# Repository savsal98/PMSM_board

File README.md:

# PMSM_board
## В данном репозитории находится проект платы управления для СДПМ.

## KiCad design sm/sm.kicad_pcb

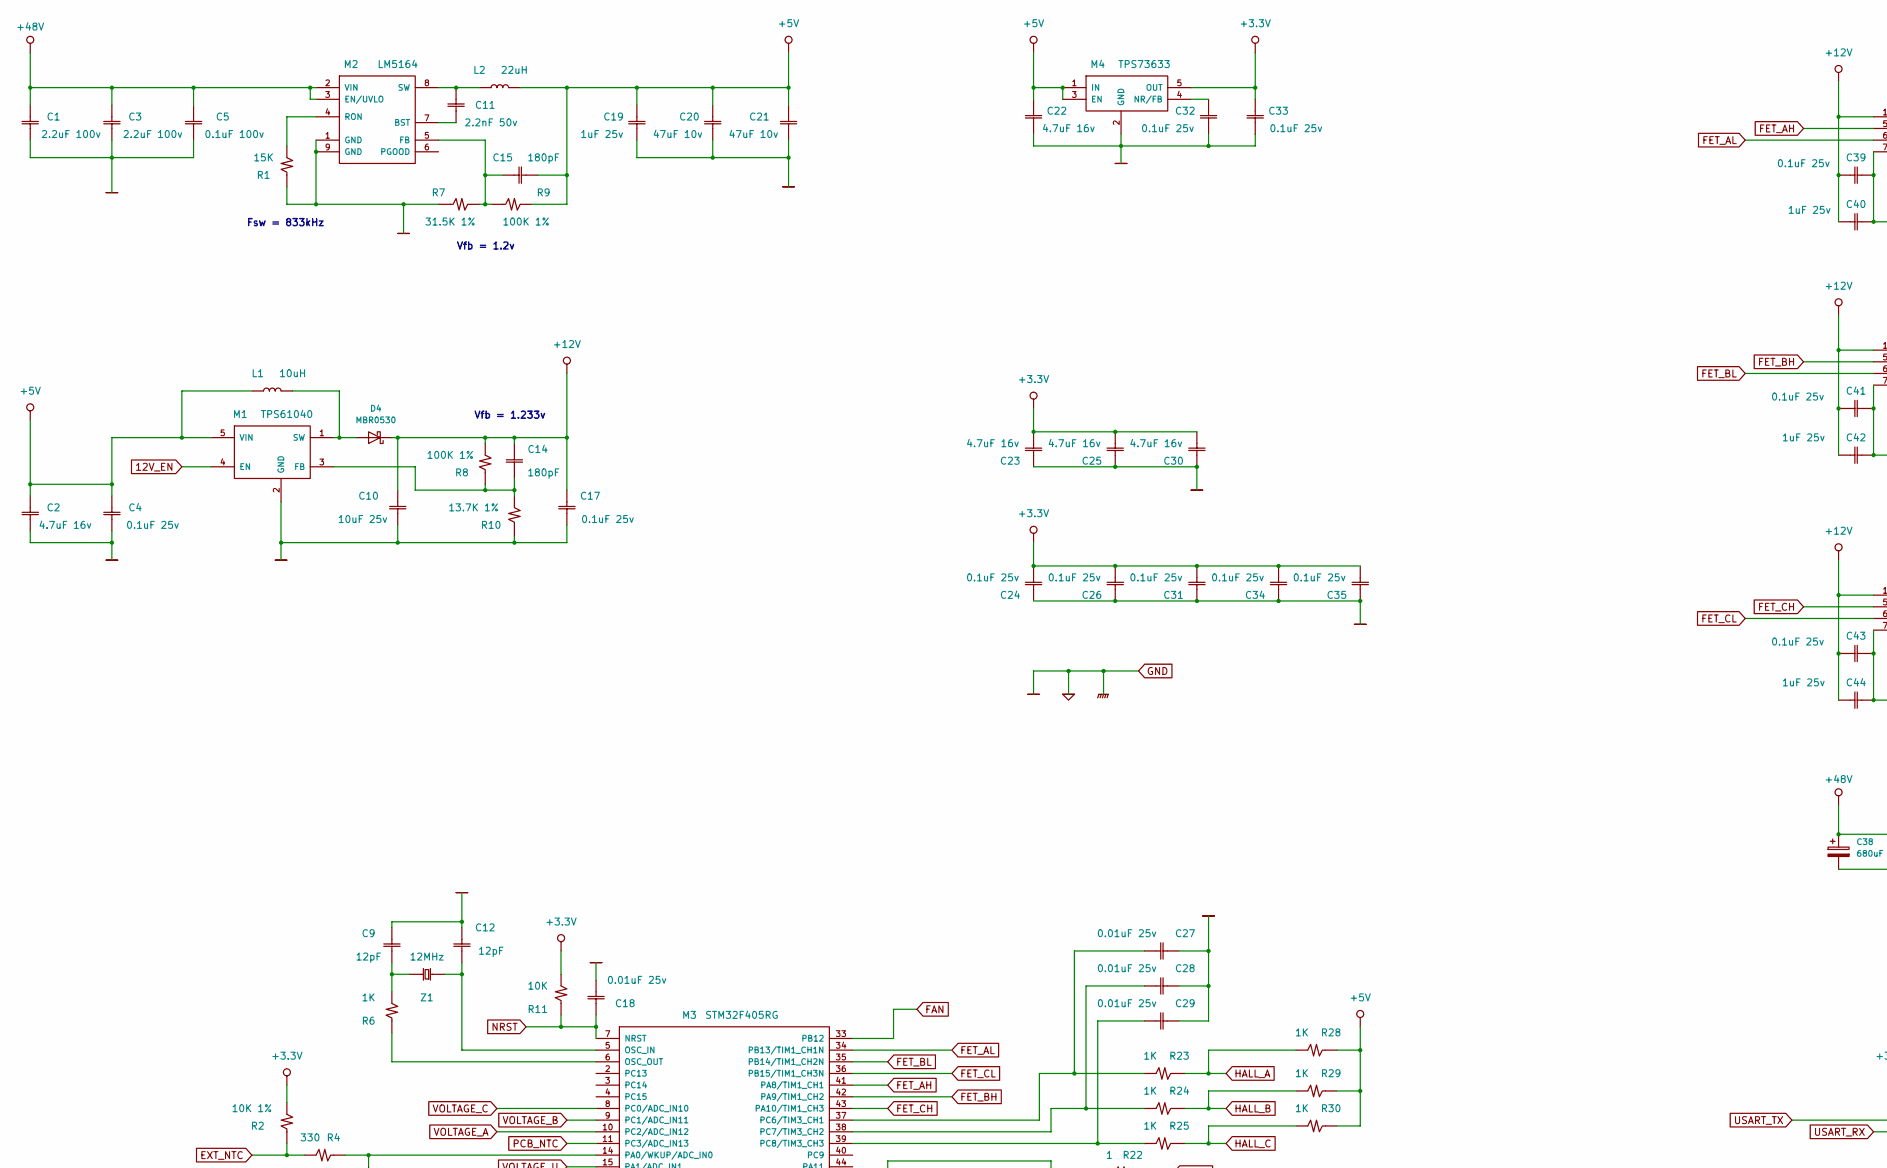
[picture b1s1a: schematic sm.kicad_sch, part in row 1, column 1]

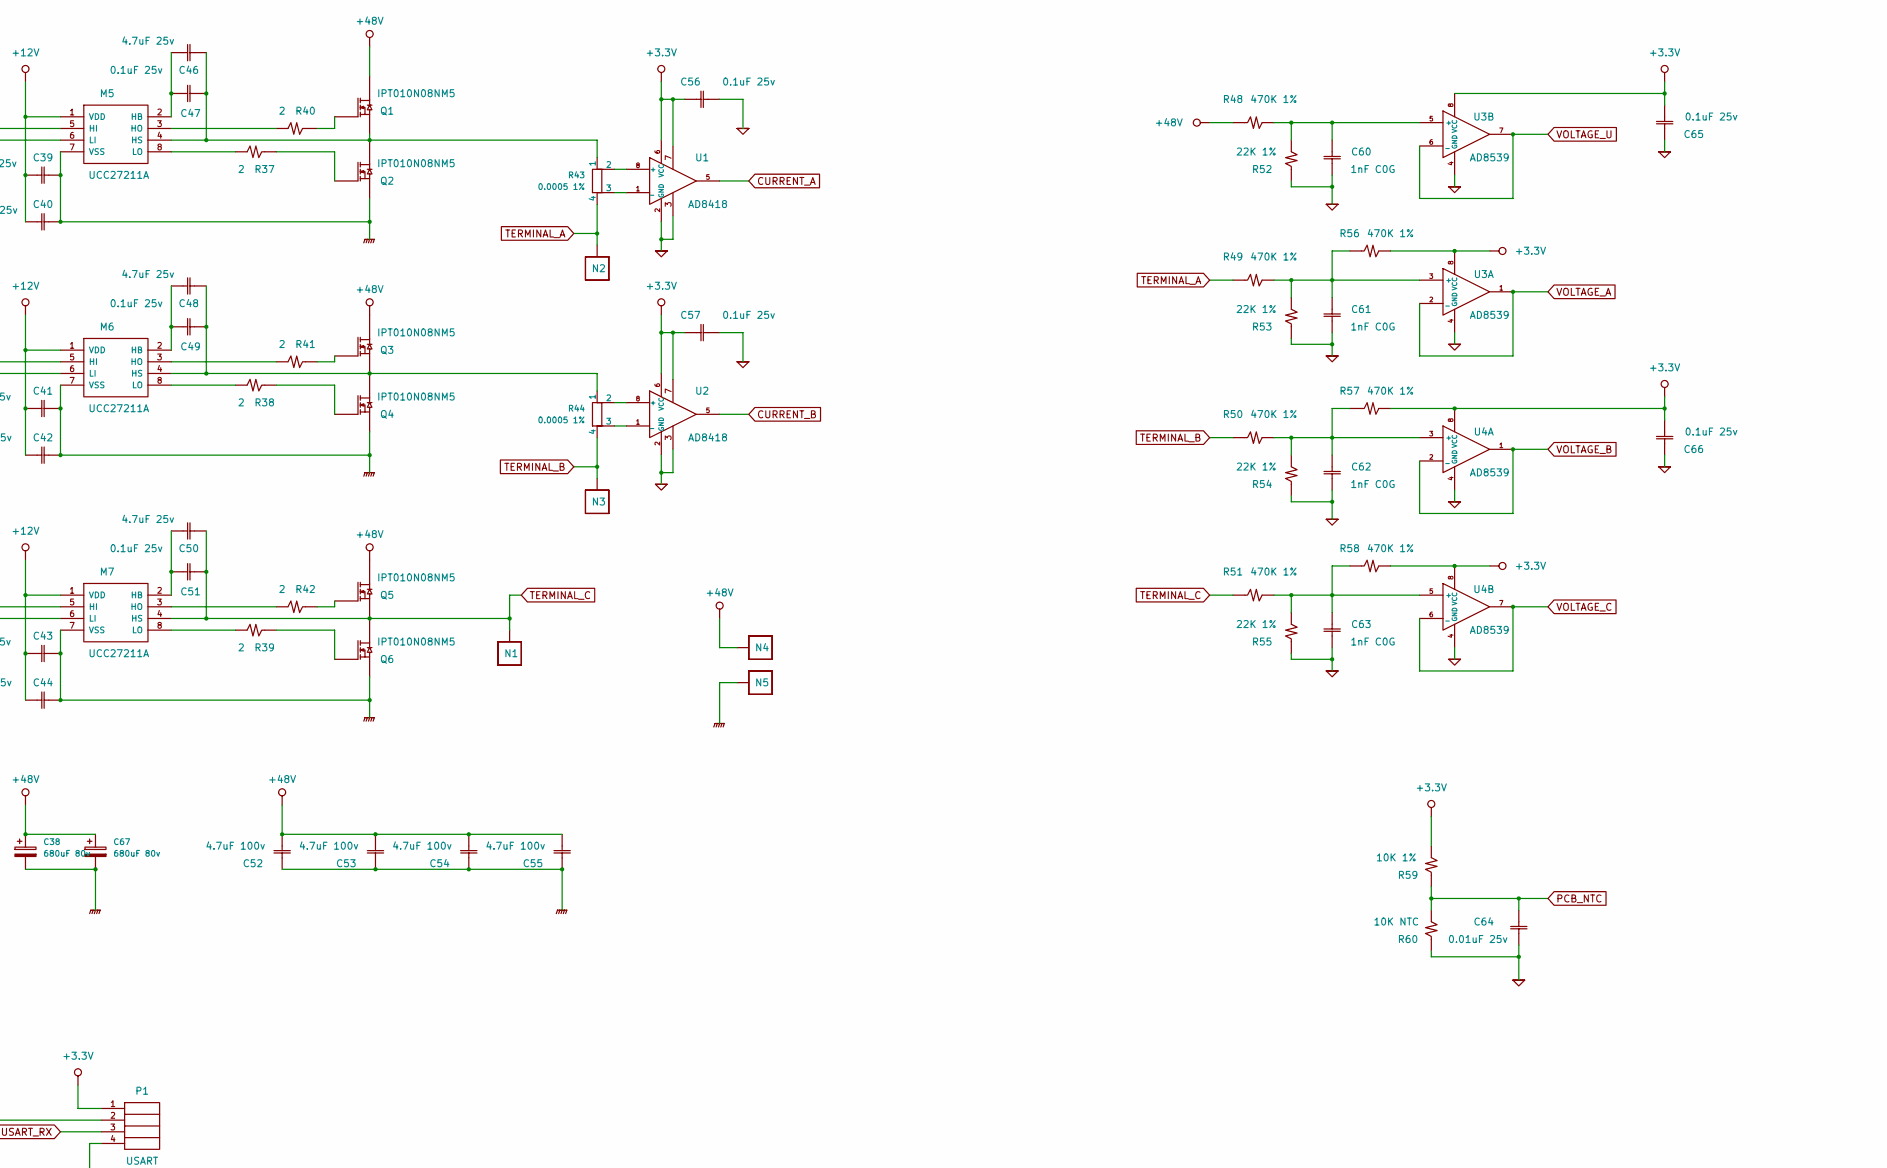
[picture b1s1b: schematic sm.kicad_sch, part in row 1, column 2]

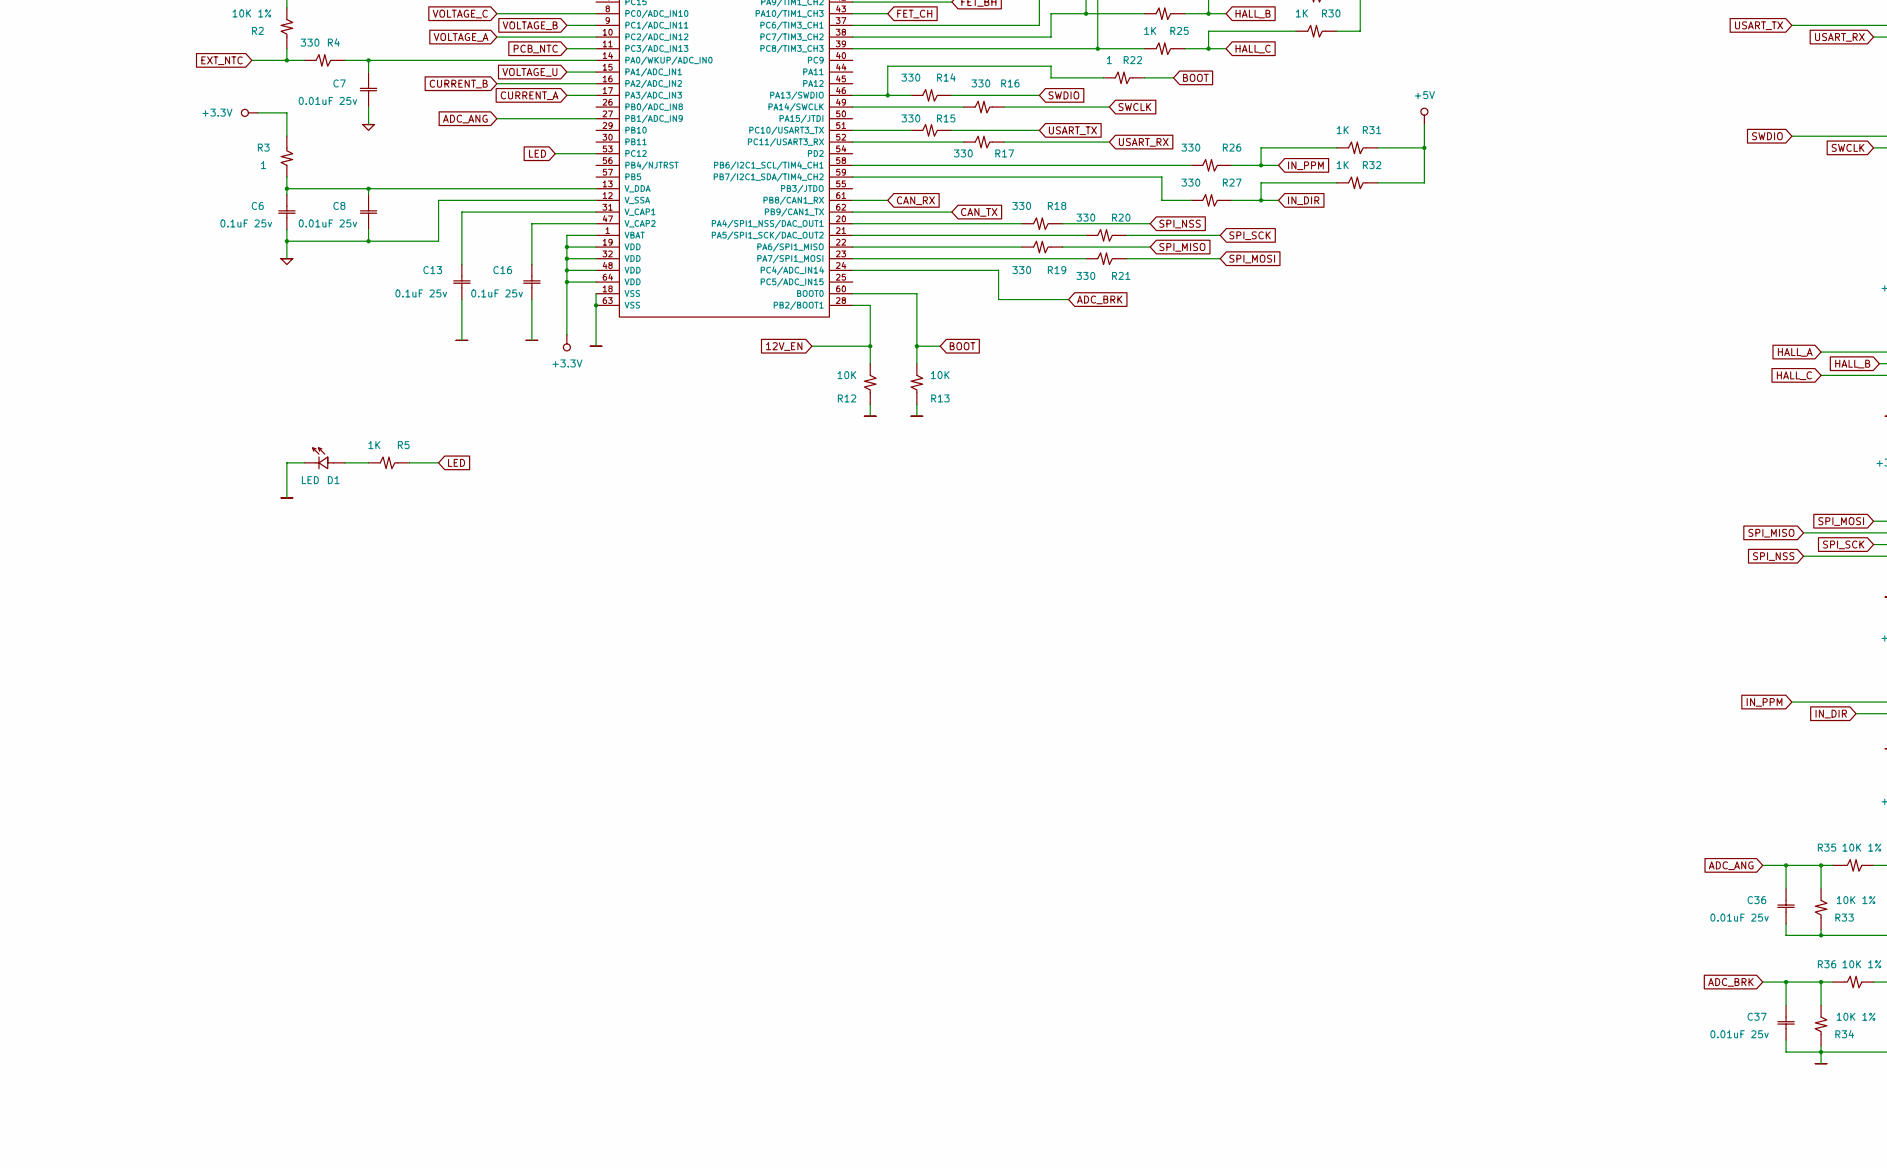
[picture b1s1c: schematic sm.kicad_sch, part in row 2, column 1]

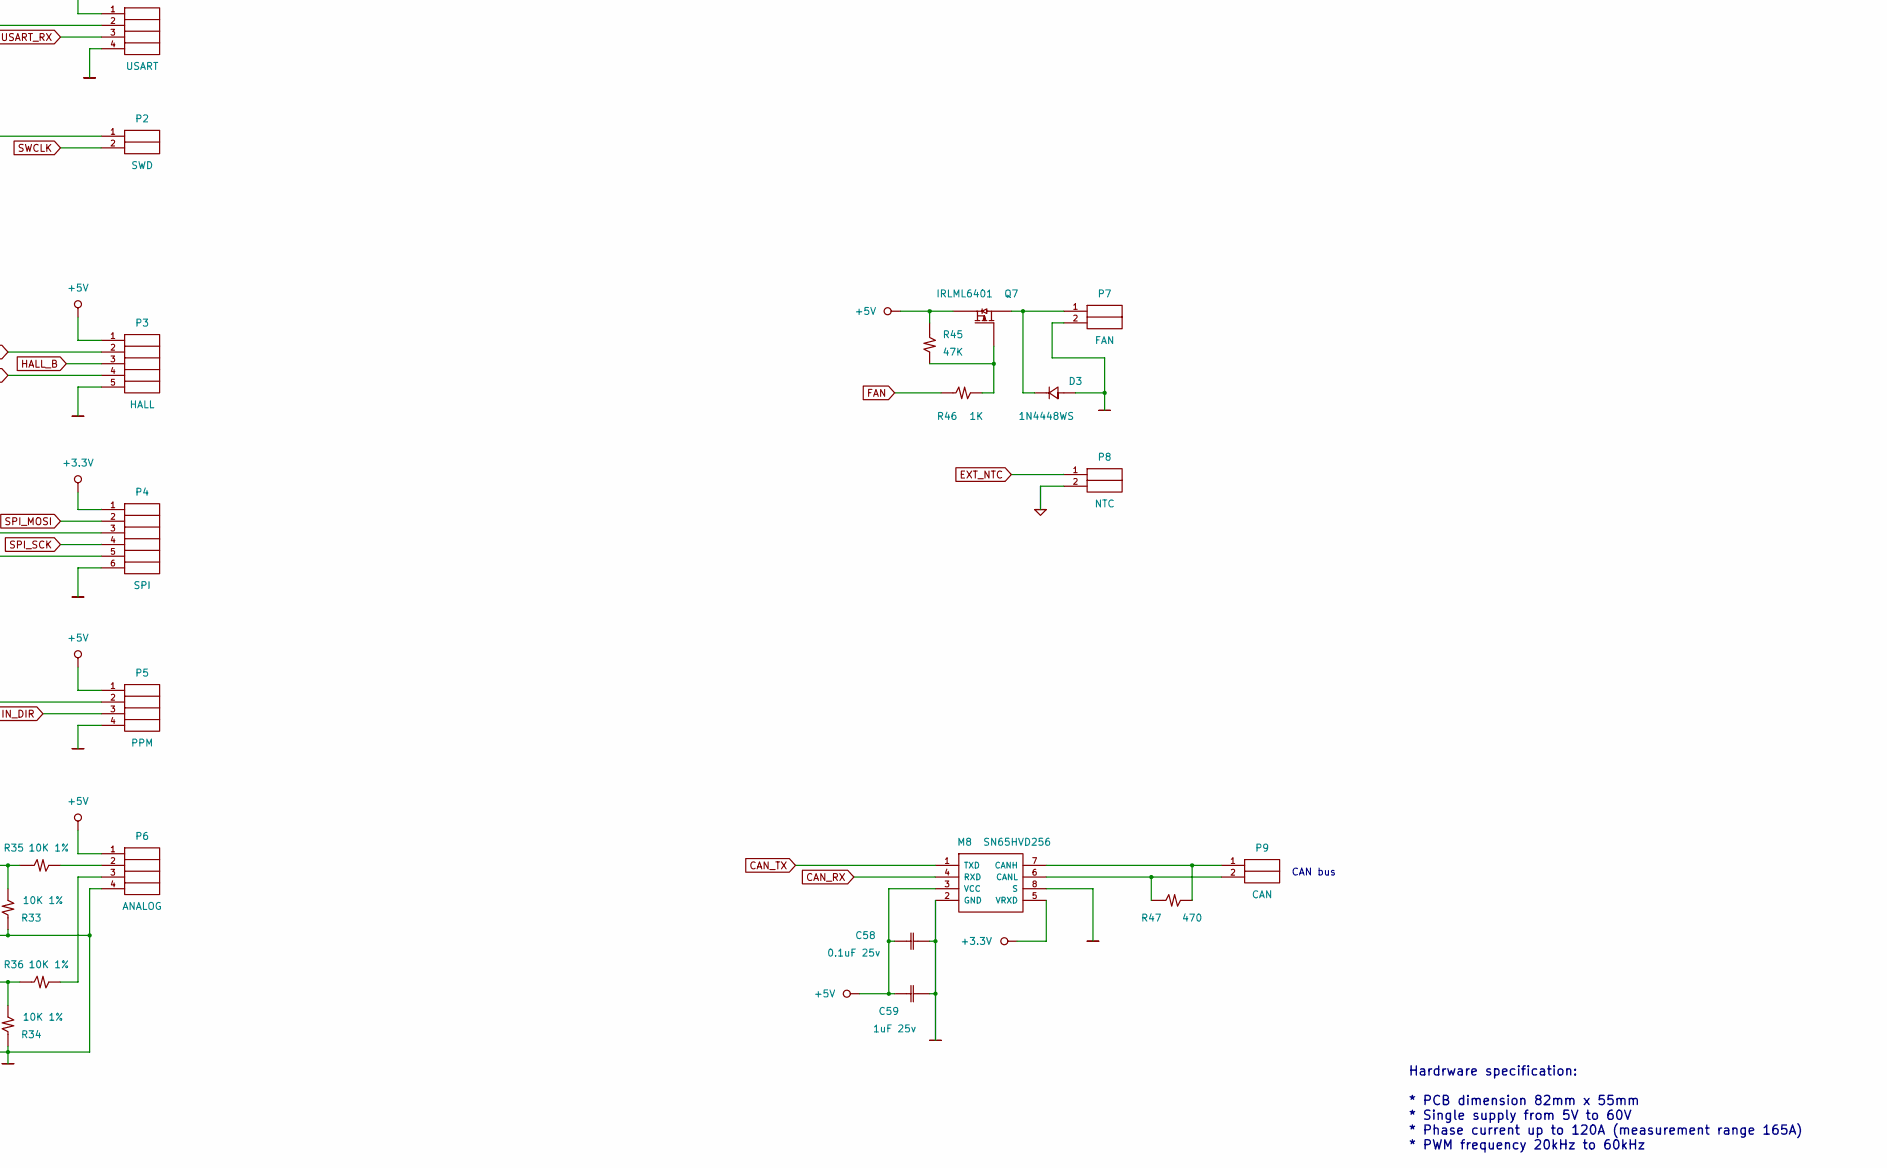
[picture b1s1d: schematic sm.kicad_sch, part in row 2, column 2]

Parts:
C1, C3: 2.2uF 100v; C_1210_3225Metric; LCSC C153036
C2, C22, C23, C25, C30: 4.7uF 16v; C_0805_2012Metric; LCSC C92762
C4, C6, C13, C16, C17, C24, C26, C31, C32, C33, C34, C35, C39, C41, C43, C47, C49, C51, C56, C57, C58, C65, C66: 0.1uF 25v; C_0805_2012Metric; LCSC C519981
C5: 0.1uF 100v; C_0805_2012Metric; LCSC C28233
C7, C8, C18, C27, C28, C29, C36, C37, C64: 0.01uF 25v; C_0603_1608Metric; LCSC C285099
C9, C12: 12pF; C_0603_1608Metric; LCSC C107034
C10: 10uF 25v; C_1210_3225Metric; LCSC C92834
C11: 2.2nF 50v; C_0805_2012Metric; LCSC C36576
C14, C15: 180pF; C_0603_1608Metric; LCSC C107041
C19, C40, C42, C44, C59: 1uF 25v; C_0805_2012Metric; LCSC C713511
C20, C21: 47uF 10v; C_1210_3225Metric; LCSC C5189825
C38, C67: 680uF 80v; CP_Radial_D16.0mm_P7.50mm; LCSC C443096
C46, C48, C50: 4.7uF 25v; C_0805_2012Metric; LCSC C1779
C52, C53, C54, C55: 4.7uF 100v; C_1210_3225Metric; LCSC C6120033
C60, C61, C62, C63: 1nF C0G; C_0603_1608Metric; LCSC C163508
D1: LED; LED_0603_1608Metric; LCSC C19171392
D3: 1N4448WS; D_0805_2012Metric; LCSC C109001
D4: MBR0530; D_SOD-123; LCSC C77336
L1: 10uH; L_Bourns_SRP1050WA; LCSC C7529415
L2: 22uH; L_Abracon_ASPI-0630LR; LCSC C7461363
M1: TPS61040; SOT-23-5; LCSC C7722
M2: LM5164; TI_SO-PowerPAD-8_ThermalVias; LCSC C477928
M3: STM32F405RG; LQFP-64_10x10mm_P0.5mm; LCSC C15742
M4: TPS73633; SOT-23-5; LCSC C28038
M5, M6, M7: UCC27211A; Texas_HSOP-8-1EP_3.9x4.9mm_P1.27mm_ThermalVias; LCSC C485921
M8: SN65HVD256; SOIC-8_3.9x4.9mm_P1.27mm; LCSC C132551
N1, N2, N3, N4, N5: PAD4; MountingHole_2.2mm_M2_Pad_Via
P1: USART; JST_PH_B4B-PH-K_1x04_P2.00mm_Vertical; LCSC C265289
P2: SWD; JST_PH_B2B-PH-K_1x02_P2.00mm_Vertical; LCSC C5251182
P3: HALL; JST_PH_B5B-PH-K_1x05_P2.00mm_Vertical; LCSC C157993
P4: SPI; JST_PH_B6B-PH-K_1x06_P2.00mm_Vertical; LCSC C495261
P5: PPM; JST_PH_B4B-PH-K_1x04_P2.00mm_Vertical; LCSC C265289
P6: ANALOG; JST_PH_B4B-PH-K_1x04_P2.00mm_Vertical; LCSC C265289
P7: FAN; JST_PH_B2B-PH-K_1x02_P2.00mm_Vertical; LCSC C5251182
P8: NTC; JST_PH_B2B-PH-K_1x02_P2.00mm_Vertical; LCSC C5251182
P9: CAN; JST_PH_B2B-PH-K_1x02_P2.00mm_Vertical; LCSC C5251182
Q1, Q2, Q3, Q4, Q5, Q6: IPT010N08NM5; Infineon_PG-HSOF-8-1_ThermalVias; LCSC C3288766
Q7: IRLML6401; TSOT-23; LCSC C2835446
R1: 15K; R_0603_1608Metric; LCSC C22809
R2, R33, R34, R35, R36, R59: 10K 1%; R_0603_1608Metric; LCSC C25804
R3, R22: 1; R_0603_1608Metric; LCSC C22936
R4, R14, R15, R16, R17, R18, R19, R20, R21, R26, R27: 330; R_0603_1608Metric; LCSC C23138
R5, R6, R23, R24, R25, R28, R29, R30, R31, R32, R46: 1K; R_0603_1608Metric; LCSC C21190
R7: 31.5K 1%; R_0603_1608Metric; LCSC C25967
R8, R9: 100K 1%; R_0603_1608Metric; LCSC C25803
R10: 13.7K 1%; R_0603_1608Metric; LCSC C22793
R11, R12, R13: 10K; R_0603_1608Metric; LCSC C25804
R37, R38, R39, R40, R41, R42: 2; R_0603_1608Metric; LCSC C22977
R43, R44: 0.0005 1%; R_Shunt_Vishay_WSK2512_6332Metric_T1.19mm; LCSC C469426
R45: 47K; R_0603_1608Metric; LCSC C25819
R47: 470; R_1206_3216Metric; LCSC C4502
R48, R49, R50, R51, R56, R57, R58: 470K 1%; R_0603_1608Metric; LCSC C23178
R52, R53, R54, R55: 22K 1%; R_0603_1608Metric; LCSC C31850
R60: 10K NTC; R_0805_2012Metric; LCSC C95968
U1, U2: AD8418; SOIC-8_3.9x4.9mm_P1.27mm; LCSC C495342
U3, U4: AD8539; SOIC-8_3.9x4.9mm_P1.27mm; LCSC C154930
Z1: 12MHz; Crystal_SMD_3225-4Pin_3.2x2.5mm; LCSC C9002

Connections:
12V_EN: M1.4 (EN), M3.28 (PB2/BOOT1), R12.2
+3.3V: C23.1, C24.1, C25.1, C26.1, C30.1, C31.1, C33.1, C34.1, C35.1, C56.2, C57.2, C65.1, C66.1, M3.1 (VBAT), M3.19 (VDD), M3.32 (VDD), M3.48 (VDD), M3.64 (VDD), M4.5 (OUT), M8.5 (VRXD), P1.1, P4.1, R2.2, R3.1, R11.2, R56.2, R57.2, R58.2, R59.2, U1.6 (VCC), U1.7, U2.6 (VCC), U2.7, U3.8 (VCC), U4.8 (VCC)
+5V: C2.1, C4.1, C15.1, C19.1, C20.1, C21.1, C22.1, C58.2, C59.2, L1.1, L2.2, M1.5 (VIN), M4.1 (IN), M4.3 (EN), M8.3 (VCC), P3.1, P5.1, P6.1, Q7.2 (S), R9.2, R28.1, R29.1, R30.1, R31.1, R32.1, R45.1
+12V: C10.1, C14.1, C17.1, C39.2, C40.1, C41.2, C42.2, C43.2, C44.2, D4.1 (K), M5.1 (VDD), M6.1 (VDD), M7.1 (VDD), R8.2
+48V: C1.2, C3.2, C5.2, C38.1, C52.1, C53.1, C54.1, C55.1, C67.1, M2.2 (VIN), M2.3 (EN/UVLO), N4.1, Q1.3 (D), Q3.3 (D), Q5.3 (D), R48.1
ADC_ANG: C36.2, M3.27 (PB1/ADC_IN9), R33.2, R35.1
ADC_BRK: C37.2, M3.24 (PC4/ADC_IN14), R34.2, R36.1
BOOT: M3.60 (BOOT0), R13.2, R22.1
CAN_RX: M3.61 (PB8/CAN1_RX), M8.4 (RXD)
CAN_TX: M3.62 (PB9/CAN1_TX), M8.1 (TXD)
CURRENT_A: M3.17 (PA3/ADC_IN3), U1.5
CURRENT_B: M3.16 (PA2/ADC_IN2), U2.5
EXT_NTC: P8.1, R2.1, R4.2
FAN: M3.33 (PB12), R46.1
FET_AH: M3.41 (PA8/TIM1_CH1), M5.5 (HI)
FET_AL: M3.34 (PB13/TIM1_CH1N), M5.6 (LI)
FET_BH: M3.42 (PA9/TIM1_CH2), M6.5 (HI)
FET_BL: M3.35 (PB14/TIM1_CH2N), M6.6 (LI)
FET_CH: M3.43 (PA10/TIM1_CH3), M7.5 (HI)
FET_CL: M3.36 (PB15/TIM1_CH3N), M7.6 (LI)
GND: C1.1, C2.2, C3.1, C4.2, C5.1, C6.2, C7.1, C8.2, C9.1, C10.2, C12.1, C13.2, C16.2, C17.2, C18.1, C19.2, C20.2, C21.2, C22.2, C23.2, C24.2, C25.2, C26.2, C27.2, C28.2, C29.2, C30.2, C31.2, C32.2, C33.2, C34.2, C35.2, C36.1, C37.1, C38.2, C39.1, C40.2, C41.1, C42.1, C43.1, C44.1, C52.2, C53.2, C54.2, C55.2, C56.1, C57.1, C58.1, C59.1, C60.2, C61.2, C62.2, C63.2, C64.1, C65.2, C66.2, C67.2, D1.1, D3.2, M1.2 (GND), M2.1 (GND), M2.9 (GND), M3.12 (V_SSA), M3.18 (VSS), M3.63 (VSS), M4.2 (GND), M5.7 (VSS), M6.7 (VSS), M7.7 (VSS), M8.2 (GND), M8.8 (S), N5.1, P1.4, P3.5, P4.6, P5.4, P6.4, P7.2, P8.2, Q2.2 (S), Q4.2 (S), Q6.2 (S), R1.1, R7.1, R10.1, R12.1, R13.1, R33.1, R34.1, R52.1, R53.1, R54.1, R55.1, R60.1, U1.2 (GND), U1.3, U2.2 (GND), U2.3, U3.4 (GND), U4.4 (GND)
HALL_A: P3.2, R23.1, R28.2
HALL_B: P3.3, R24.1, R29.2
HALL_C: P3.4, R25.1, R30.2
IN_DIR: P5.3, R27.1, R32.2
IN_PPM: P5.2, R26.1, R31.2
LED: M3.53 (PC12), R5.1
NC: U1.4 (NC), U2.4 (NC)
NRST: C18.2, M3.7 (NRST), R11.1
unnamed: C9.2, R6.2, Z1.1
unnamed: D1.2, R5.2
unnamed: D4.2 (A), L1.2, M1.1 (SW)
unnamed: C14.2, M1.3 (FB), R8.1, R10.2
unnamed: C11.2, M2.7 (BST)
unnamed: C15.2, M2.5 (FB), R7.2, R9.1
unnamed: M2.4 (RON), R1.2
unnamed: C11.1, L2.1, M2.8 (SW)
unnamed: C12.2, M3.5 (OSC_IN), Z1.2
unnamed: M3.6 (OSC_OUT), R6.1
unnamed: C7.2, M3.14 (PA0/WKUP/ADC_IN0), R4.1
unnamed: M3.20 (PA4/SPI1_NSS/DAC_OUT1), R18.2
unnamed: M3.21 (PA5/SPI1_SCK/DAC_OUT2), R20.2
unnamed: M3.22 (PA6/SPI1_MISO), R19.2
unnamed: M3.23 (PA7/SPI1_MOSI), R21.2
unnamed: M3.46 (PA13/SWDIO), R14.2, R22.2
unnamed: M3.49 (PA14/SWCLK), R16.2
unnamed: M3.58 (PB6/I2C1_SCL/TIM4_CH1), R26.2
unnamed: M3.59 (PB7/I2C1_SDA/TIM4_CH2), R27.2
unnamed: C27.1, M3.37 (PC6/TIM3_CH1), R23.2
unnamed: C28.1, M3.38 (PC7/TIM3_CH2), R24.2
unnamed: C29.1, M3.39 (PC8/TIM3_CH3), R25.2
unnamed: M3.51 (PC10/USART3_TX), R15.2
unnamed: M3.52 (PC11/USART3_RX), R17.2
unnamed: C13.1, M3.31 (V_CAP1)
unnamed: C16.1, M3.47 (V_CAP2)
unnamed: C6.1, C8.1, M3.13 (V_DDA), R3.2
unnamed: C32.1, M4.4 (NR/FB)
unnamed: C46.2, C47.2, M5.2 (HB)
unnamed: M5.3 (HO), R40.2
unnamed: C46.1, C47.1, M5.4 (HS), Q1.2 (S), Q2.3 (D), R43.1
unnamed: M5.8 (LO), R37.2
unnamed: C48.2, C49.2, M6.2 (HB)
unnamed: M6.3 (HO), R41.2
unnamed: C48.1, C49.1, M6.4 (HS), Q3.2 (S), Q4.3 (D), R44.1
unnamed: M6.8 (LO), R38.2
unnamed: C50.2, C51.2, M7.2 (HB)
unnamed: M7.3 (HO), R42.2
unnamed: M7.8 (LO), R39.2
unnamed: M8.7 (CANH), P9.1, R47.2
unnamed: M8.6 (CANL), P9.2, R47.1
unnamed: P6.2, R35.2
unnamed: P6.3, R36.2
unnamed: Q1.1 (G), R40.1
unnamed: Q2.1 (G), R37.1
unnamed: Q3.1 (G), R41.1
unnamed: Q4.1 (G), R38.1
unnamed: Q5.1 (G), R42.1
unnamed: Q6.1 (G), R39.1
unnamed: D3.1, P7.1, Q7.3 (D)
unnamed: Q7.1 (G), R45.2, R46.2
unnamed: R43.2, U1.8 (+)
unnamed: R43.3, U1.1 (_)
unnamed: R44.2, U2.8 (+)
unnamed: R44.3, U2.1 (_)
unnamed: C61.1, R49.2, R53.2, R56.1, U3.3 (+)
unnamed: C60.1, R48.2, R52.2, U3.5 (+)
unnamed: C62.1, R50.2, R54.2, R57.1, U4.3 (+)
unnamed: C63.1, R51.2, R55.2, R58.1, U4.5 (+)
PCB_NTC: C64.2, M3.11 (PC3/ADC_IN13), R59.1, R60.2
SPI_MISO: P4.3, R19.1
SPI_MOSI: P4.2, R21.1
SPI_NSS: P4.5, R18.1
SPI_SCK: P4.4, R20.1
SWCLK: P2.2, R16.1
SWDIO: P2.1, R14.1
TERMINAL_A: N2.1, R43.4, R49.1
TERMINAL_B: N3.1, R44.4, R50.1
TERMINAL_C: C50.1, C51.1, M7.4 (HS), N1.1, Q5.2 (S), Q6.3 (D), R51.1
USART_RX: P1.3, R17.1
USART_TX: P1.2, R15.1
VOLTAGE_A: M3.10 (PC2/ADC_IN12), U3.1, U3.2 (_)
VOLTAGE_B: M3.9 (PC1/ADC_IN11), U4.1, U4.2 (_)
VOLTAGE_C: M3.8 (PC0/ADC_IN10), U4.6 (_), U4.7
VOLTAGE_U: M3.15 (PA1/ADC_IN1), U3.6 (_), U3.7

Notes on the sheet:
Hardrware specification: * PCB dimension 82mm x 55mm * Single supply from 5V to 60V * Phase current up to 120A (measurement range 165A) * PWM frequency 20kHz to 60kHz
Vfb = 1.2v
Vfb = 1.233v
CAN bus
Fsw = 833kHz

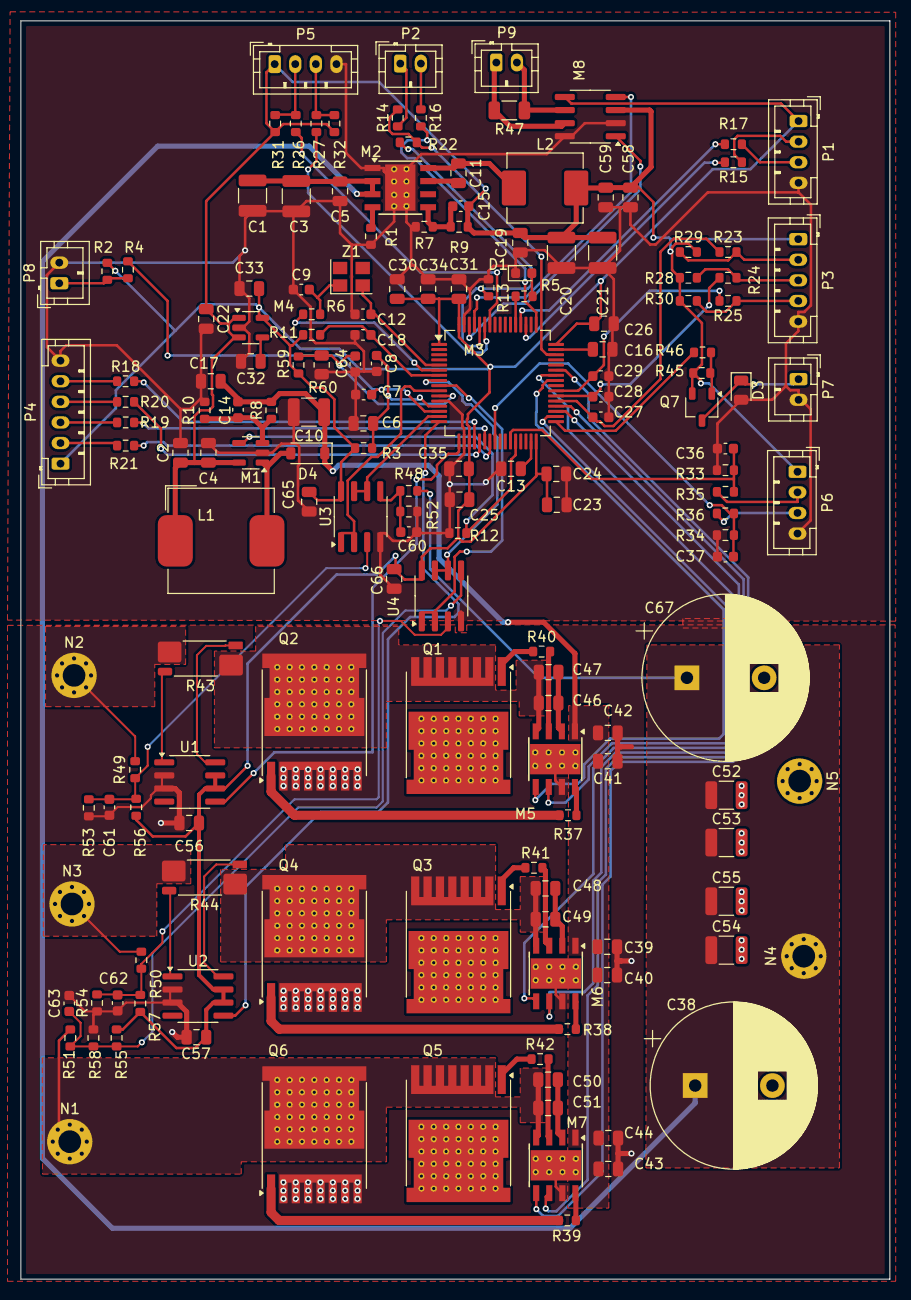
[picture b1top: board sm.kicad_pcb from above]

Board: 2 copper layers, 84.4 x 122.2 mm, 165 parts (0 on the bottom side), 104 nets.

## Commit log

2024-04-17 Add kicad project
2024-04-23 Change location of the ports
2024-04-25 Use freerouting
2024-05-03 Trace tracks
    Select components
2024-05-03 Fix cosmetic
2024-05-08 fix errors
2024-05-15 Fix pcbs
